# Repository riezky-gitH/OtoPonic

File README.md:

# Otomatisasi Hidroponik Berbasis IoT dengan Kendali Jarak Jauh dan Aplikasi Real-Time.
### Solusi Pertanian Cerdas Masa Kini

## Daftar Isi

1. [Deskripsi Produk](https://github.com/riezky-gitH/OtoPonic#deskripsi-produk)
2. [Struktur Tim](https://github.com/riezky-gitH/OtoPonic#team-member)
3. [Tujuan Produk](https://github.com/riezky-gitH/OtoPonic#tujuan)
4. [Keunggulan Produk](https://github.com/riezky-gitH/OtoPonic#keunggulan)
5. [Potensi Pengembangan](https://github.com/riezky-gitH/OtoPonic#potensi-pengembangan)
6. [Kolaborasi & Dukungan](https://github.com/riezky-gitH/OtoPonic#kolaborasi--dukungan)
7. [Hardware](https://github.com/riezky-gitH/OtoPonic#hardware)
8. [Software](https://github.com/riezky-gitH/OtoPonic#software)
9. [Aplikasi OtoPonic](https://github.com/riezky-gitH/OtoPonic#aplikasi-otoponic)
10. [Hubungi Kami](https://github.com/riezky-gitH/OtoPonic#hubungi-kami)

## Deskripsi Produk
**OtoPonic** adalah solusi pertanian cerdas berbasis IoT yang dirancang untuk mengotomatisasikan hidroponik dengan fitur pemantauan real-time dan kendali jarak jauh melalui aplikasi atau web. Sistem ini mampu memantau berbagai parameter penting seperti pH air, kadar nutrisi, suhu air, serta batas ketinggian air dalam pipa hidroponik. OtoPonic dilengkapi dengan fitur kontrol otomatis, seperti aktivasi pompa nutrisi saat kadar terlalu rendah, pengaturan pH air dengan pompa pH up/down, dan penyiraman atau pengurasan otomatis dalam instalasi hidroponik. Selain itu, pengguna juga dapat mengontrol sistem secara manual melalui dashboard yang intuitif serta menerima notifikasi saat terjadi kondisi abnormal. Proyek ini bertujuan untuk meningkatkan efisiensi dan kenyamanan dalam bercocok tanam hidroponik, terutama bagi pengguna yang ingin memantau dan mengelola kebun mereka dari jarak jauh secara praktis dan real-time.

## Support By 
>- Dosen Pengampu : Akhmad Hendriawan ST., MT. (NIP.197501272002121003)
>- Mata kuliah : Mikrokontroller
>- Program Studi : D4 Teknik Elektronika
>- Politeknik Elektronika Negeri Surabaya<br>

## Team Member
|      NRP      |       Nama      |    Jobdesk    |   Akun |
| :-----------:|:----------------:| :------------:| :-----:|
| 2123600003    | Taufiq  |  UI/UX Designer      | [Taufiq](https://github.com/Raditya-G)
| 2123600006    | Auliya         |   UI/UX Designer | [Auilya](https://github.com/auliyarzk/)
| 2123600017    | Brian         |    Programmer      | [Brian](https://github.com/brianrjg)
| 2123600018    | Riezky                | Project Manager | [Riezky](https://github.com/riezky-gitH)
| 2123600020    | Subkhi               | Hardware Developer     | [Subkhi](https://github.com/subkhiMuhammad)
| 2123600024    | Alwan               | 3D Designer     |[Alwan](https://github.com/alwan441)

## Foto Anggota Tim 

## Tujuan
- **Mempermudah perawatan kebun hidroponik** dengan sistem otomatis yang mengatur pH, nutrisi, dan penyiraman secara mandiri.
- **Memantau kondisi tanaman secara real-time** melalui aplikasi atau web, kapan saja dan di mana saja.
- **Memberikan kontrol penuh jarak jauh**, sehingga pengguna bisa mengelola kebun tanpa harus selalu berada di lokasi.
- **Meningkatkan efisiensi dan hasil panen** dengan pengelolaan nutrisi dan air yang lebih akurat dan stabil.
- **Cocok untuk semua kalangan**, mulai dari petani pemula hingga profesional yang ingin solusi praktis dan modern.

## Keunggulan

- **Integrasi IoT** yang kuat dengan adanya sensor dan komunikasi data berbasis GSM untuk pemantauan jarak jauh yang stabil
- **Kontrol manual & otomatis** yang dapat memberikan fleksibilitas
- **Antarmuka pengguna** yang intuitif dalam penggunaan UI/UX
- **Mendukung keberlanjutan & efisiensi energi** dalam mengurangi limbah air dan penggunaa sumber daya berlebihan

## Potensi Pengembangan OtoPonic
- **IoT Cloud** – Akses global & notifikasi real-time.
- **Peringatan WhatsApp/SMS** – Info langsung saat kondisi kritis.
- **AI & Machine Learning** – Prediksi kebutuhan nutrisi & pertumbuhan.
- **Smart City Ready** – Siap terintegrasi dengan infrastruktur kota pintar.
- **Dashboard Analytics** – Visualisasi data & performa tanaman.

## Kolaborasi & Dukungan
- **Investor Teknologi** – Skala produksi & fitur lebih canggih.
- **Startup/R&D** – Kolaborasi pengembangan sensor & AI.
- **Kampus/Inkubator** – Edukasi & riset pertanian cerdas.
- **Pemerintah & Komunitas** – Implementasi urban farming pintar.
- **UMKM & Petani Modern** – Otomatisasi untuk hasil lebih optimal.
  
## Hardware
### 1. Desain Skematik

### 2. Desain PCB

### 3. 3D Desain PCB

## Software
### 1. Blok Diagram

### 2. Diagram Arsitektur Sistem

## Aplikasi OtoPonic
### 1. Login

### 2. Dashboard

### 3. Data Riwayat

### 4. Parameter Setting
)

## Hubungi Kami

Untuk kerja sama, pertanyaan, atau demo proyek:

**Email Project Manager**: [riezky.mochammad07@gmail.com](mailto:riezky.mochammad07@gmail.com)

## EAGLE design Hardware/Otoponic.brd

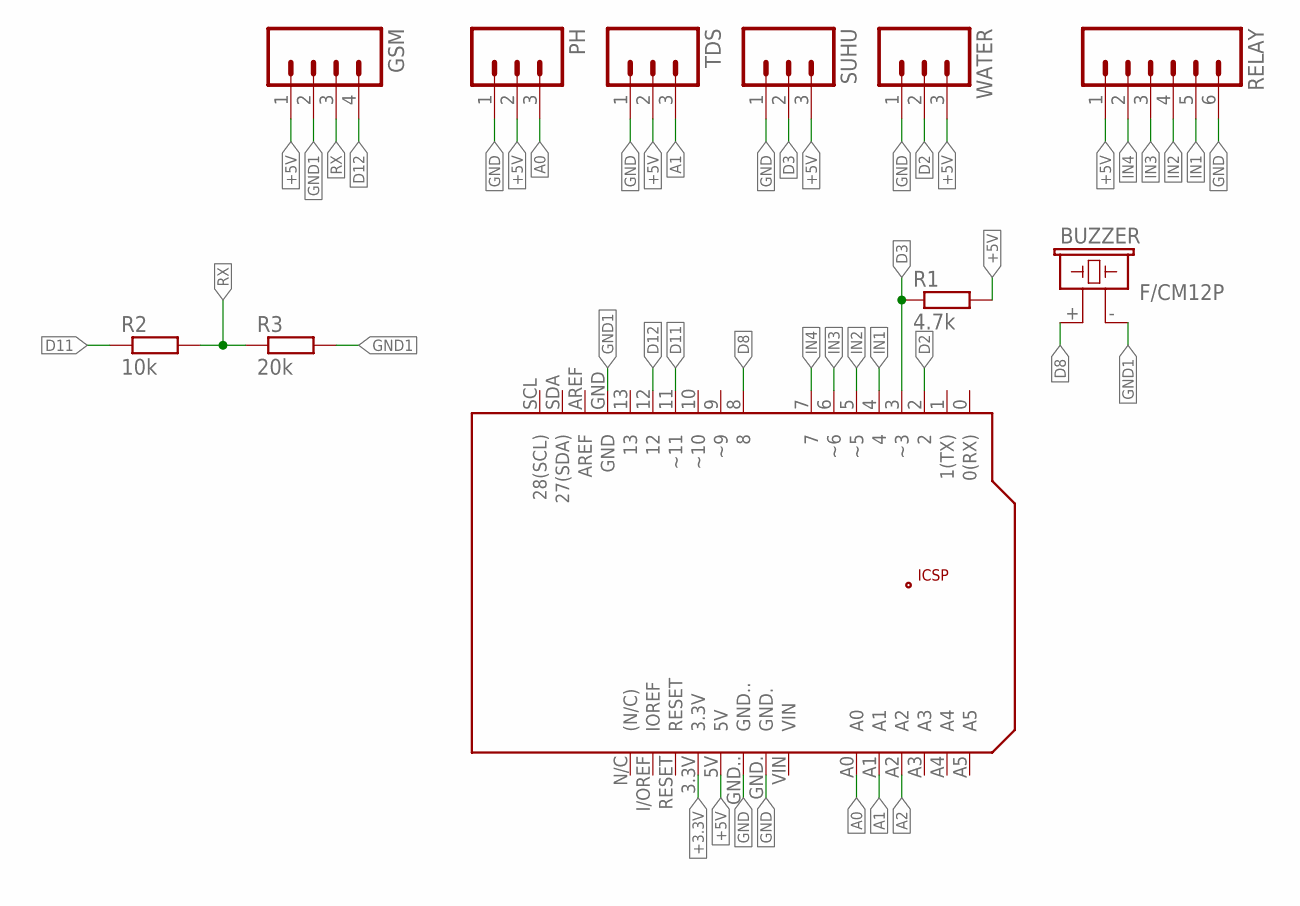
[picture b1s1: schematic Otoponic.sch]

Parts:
BUZZER: F/CM12P
GSM: M04; 04P
PCB2: ARDUINO_UNO
PH: M03; 03P
R1: 4.7k; 0207/10
R2: 10k; 0207/10
R3: 20k; 0207/10
RELAY: M06; 06P
SUHU: M03; 03P
TDS: M03; 03P
WATER: M03; 03P

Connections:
+3.3V: PCB2.3.3V
+5V: GSM.1, PCB2.5V, PH.2, R1.2, RELAY.1, SUHU.3, TDS.2, WATER.3
A0: PCB2.A0, PH.3
A1: PCB2.A1, TDS.3
A2: PCB2.A2
D2: PCB2.2, WATER.2
D3: PCB2.3 (~3), R1.1, SUHU.2
D8: BUZZER.+ (1), PCB2.8
D11: PCB2.11 (~11), R2.1
D12: GSM.4, PCB2.12
GND: PCB2.GND., PCB2.GND.., PH.1, RELAY.6, SUHU.1, TDS.1, WATER.1
GND1: BUZZER.- (2), GSM.2, PCB2.GND, R3.2
IN1: PCB2.4, RELAY.5
IN2: PCB2.5 (~5), RELAY.4
IN3: PCB2.6 (~6), RELAY.3
IN4: PCB2.7, RELAY.2
RX: GSM.3, R2.2, R3.1

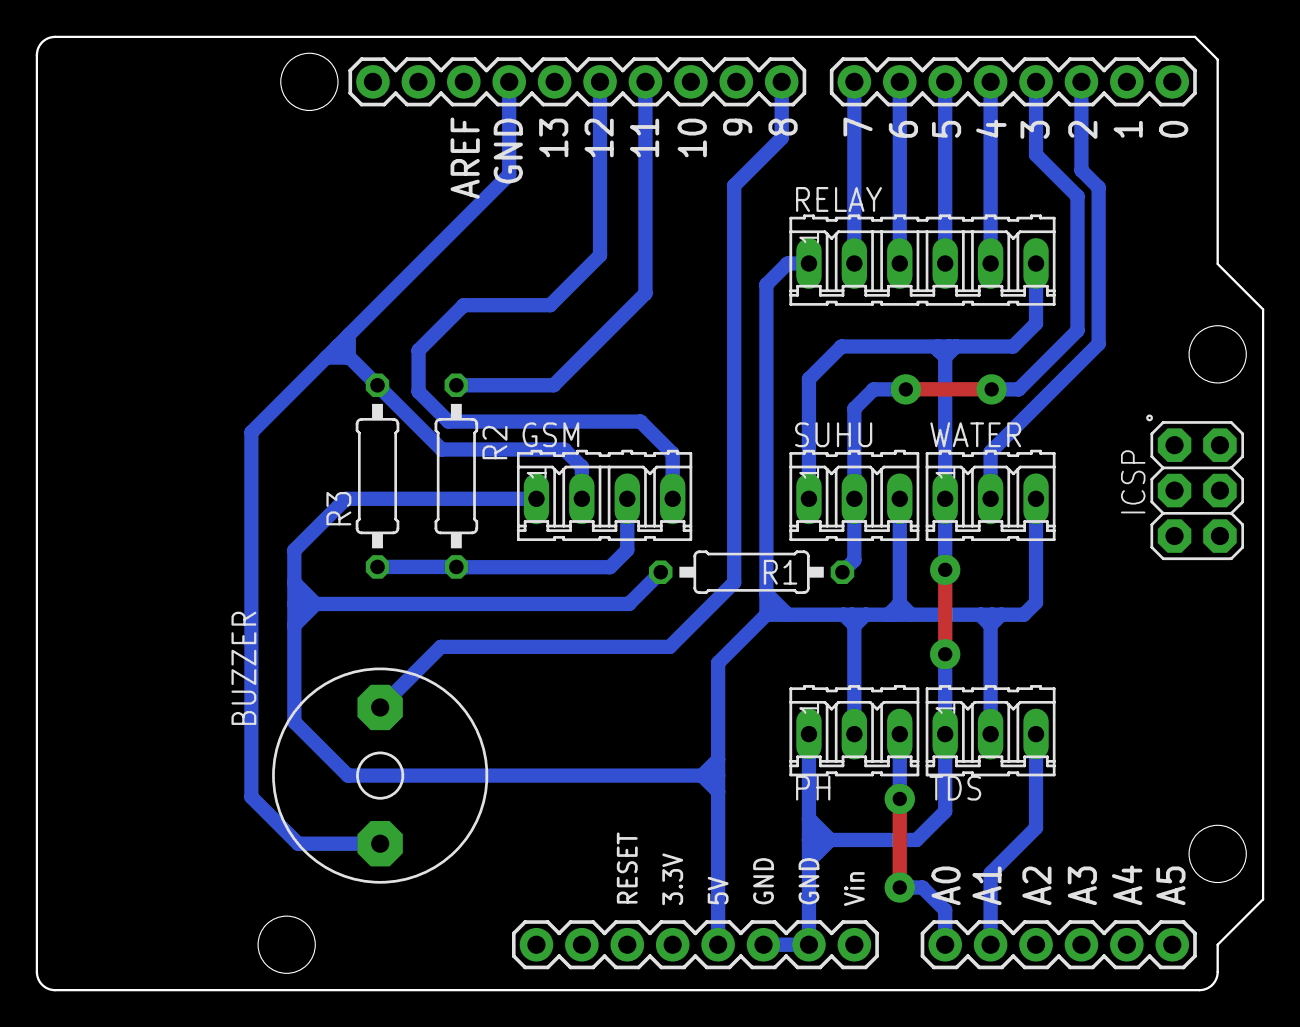
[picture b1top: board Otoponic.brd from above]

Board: 2 copper layers, 68.6 x 53.3 mm, 11 parts (0 on the bottom side), 15 nets.

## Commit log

2025-05-06 Create ppt
2025-05-16 Create Dokumentasi
    Project Otoponic dari J-Team ini berfungsi sebagai solusi pertanian cerdas berbasis IoT yang dirancang untuk mengotomatiskan sistem hidroponik dengan fitur pemantauan real-time dan pengendalian jarak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
2025-05-16 Create D
2025-06-02 Pesan commit pertama
2025-06-02 Second commit
2025-06-02 File PCB
    File Skematik dan File Board
2025-06-02 Preview
    Preview desain Skematik dan PCB
2025-06-03 first commite
2025-06-03 thirt commit
2025-06-03 second commite
2025-06-03 Preview
    Preview simulasi menggunakan website wokwi
2025-06-03 Link Simulasi.txt
    Link project wokwi
2025-06-03 Link Simulasi
    Link simulasi yang ada di wokwi
2025-06-03 README.md
